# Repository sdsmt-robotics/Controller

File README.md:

# ARCHIVED. USE GITLAB.

# Controller
Repo is used to document all the iterations for the controller

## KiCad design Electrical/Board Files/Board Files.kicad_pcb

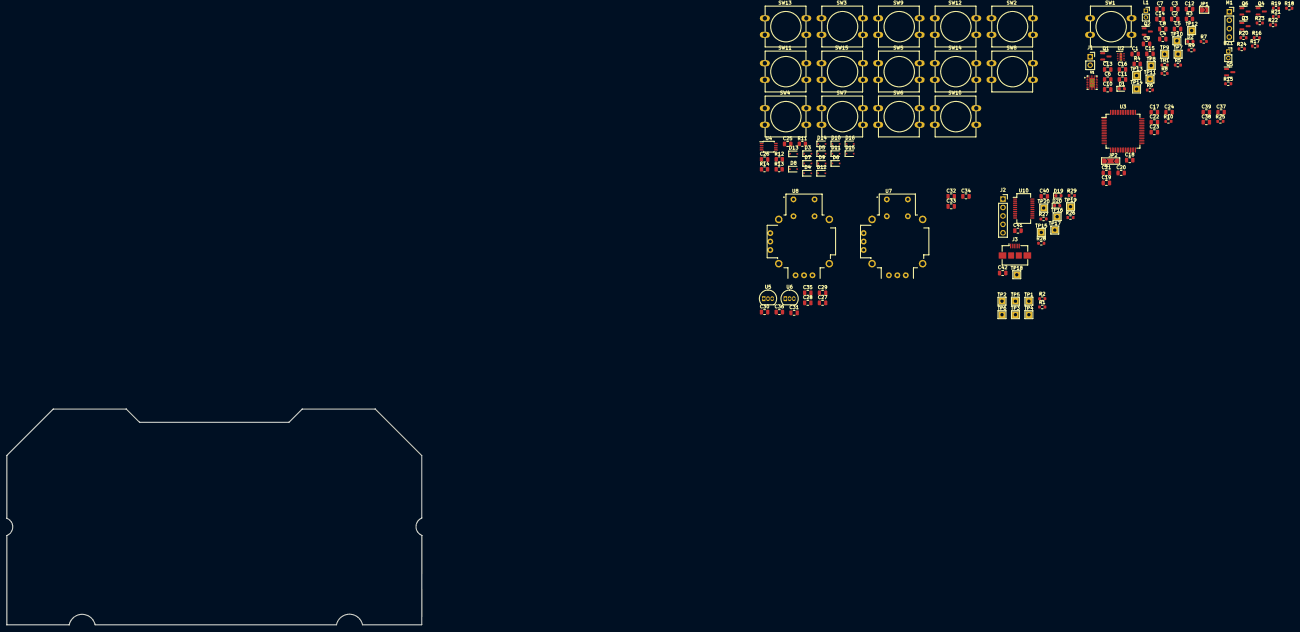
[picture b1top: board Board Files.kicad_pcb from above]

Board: 2 copper layers, 125.1 x 65.0 mm, 148 parts (0 on the bottom side), 94 nets, no tracks yet.

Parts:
BZ1: Buzzer; PinSocket_1x02_P2.00mm_Vertical
C1, C5, C6, C13, C19, C20, C25, C27, C29, C30, C31, C32, C35, C37, C38, C40: 1u; C_0805_2012Metric
C2, C7, C8, C9, C11, C21, C22, C23, C24, C26, C33, C34, C41, C42: 0.1u; C_0805_2012Metric
C3, C4, C10, C12, C17, C18, C39: 10u; C_0805_2012Metric
C14, C15, C16: 22u; C_0805_2012Metric
C28, C36: 0.01u; C_0805_2012Metric
D1: CHARGE_LED; LED_0603_1608Metric
D2: PWR_LED; LED_0603_1608Metric
D3, D4, D5, D6, D7, D8, D9, D10, D11, D12, D13, D14, D15, D16: BAT54J; D_SOD-323F
D19: RX_LED; LED_0603_1608Metric
D20: TX_LED; LED_0603_1608Metric
J1: BATT; PinSocket_1x02_P2.54mm_Vertical
J2: DEBUG; PinSocket_1x05_P2.54mm_Vertical
J3: USB_B_Micro; USB_Micro-B_Amphenol_10104110_Horizontal
JP1: SolderJumper_3_Open; SolderJumper-2_P1.3mm_Open_TrianglePad1.0x1.5mm
JP2: SolderJumper_2_Open; SolderJumper-3_P2.0mm_Open_TrianglePad1.0x1.5mm
L1: 1.5uH; PinSocket_1x02_P2.00mm_Vertical
M1: Motor_DC; PinSocket_1x04_P2.54mm_Vertical
Q1, Q2: PJA3411; SOT-23
Q3, Q4, Q5, Q6: BSS138; SOT-23
R1, R2: 4k; R_0603_1608Metric
R3, R4: 10; R_0805_2012Metric
R5: 1k; R_0603_1608Metric
R6, R7: 220; R_0603_1608Metric
R8: 768k; R_0603_1608Metric
R9: 137k; R_0603_1608Metric
R10, R18, R19, R23, R24, R25: 10k; R_0603_1608Metric
R11, R12, R13, R14: 10k; R_0805_2012Metric
R15, R20: 30; R_0603_1608Metric
R16, R17, R21, R22: 100; R_0603_1608Metric
R26, R27: 27R; R_0603_1608Metric
R28, R29: 270R; R_0603_1608Metric
SW1: SW_DIP_x01; SW_PUSH-12mm
SW2, SW3, SW4, SW5, SW6, SW7, SW8, SW9, SW10, SW11, SW12, SW13, SW14, SW15: SW_PUSH-12mm
TH1: 47K; R_0603_1608Metric
TP1, TP2, TP3, TP4, TP5, TP6, TP7, TP8, TP9, TP10, TP11, TP12, TP13, TP14, TP15, TP16, TP17, TP18, TP19, TP20: TestPoint; TestPoint_THTPad_2.0x2.0mm_Drill1.0mm
U1: TPS63020; IC_TPS63020DSJR
U2: BQ25050DQCR; WSON-10-1EP_2x3mm_P0.5mm_EP0.84x2.4mm_ThermalVias
U3: STM32L431RCTx; LQFP-64_10x10mm_P0.5mm
U4: 74LVC3G17; TSSOP-8_3x3mm_P0.65mm
U5, U6: DRV5055A2xLPGxQ1; TO-92_Inline
U7, U8: COM-09032; XDCR_COM-09032
U10: FT231XS; SSOP-20_3.9x8.7mm_P0.635mm

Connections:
+3V3: BZ1.1 (-), C1.1, C2.1, C10.1, C12.1, C13.1, C14.1, C15.1, C16.1, C17.1, C18.1, C19.1, C20.1, C21.1, C22.1, C23.1, C24.1, C25.1, C26.1, C27.1, C28.1, C31.1, C32.1, C33.1, C34.1, C35.1, C36.1, C37.1, C38.1, C39.1, D2.2 (A), J2.1, M1.1 (+), Q1.3 (D), Q2.3 (D), R1.1, R2.1, R8.1, R10.1, R25.2, SW1.2, TP9.1, TP13.1, U1.4 (VOUT), U1.5 (VOUT), U2.6 (BAT), U3.1 (VBAT), U3.13 (VDDA), U3.19 (VDD), U3.32 (VDD), U3.48 (VDD), U3.64 (VDD), U4.8 (VCC), U5.1 (VCC), U6.1 (VCC), U7.B1B (S1), U7.B2B (BB), U7.H1, U7.V1, U8.B1B (S1), U8.B2B (BB), U8.H1, U8.V1
/Debug/CTS_B: TP16.1, U10.9 (~CTS)
/Debug/DCD_B: TP19.1, U10.8 (~DCD)
/Debug/DSR_B: TP18.1, U10.7 (~DSR)
/Debug/DTR_B: TP17.1, U10.1 (~DTR)
/Debug/FUART.RX: U3.42 (PA9), U10.20 (TXD)
/Debug/FUART.TX: U3.43 (PA10), U10.4 (RXD)
/Debug/RI_B: TP20.1, U10.5 (~RI)
/Debug/RTS_B: TP15.1, U10.2 (~RTS)
/Debug/RX_LED_B: D19.1 (K), U10.17 (CBUS1)
/Debug/SWD.CLK: J2.3, U3.49 (PA14)
/Debug/SWD.DATA: J2.2, U3.46 (PA13)
/Debug/SWD.NRST: J2.4, JP2.2 (B), R10.2, U3.7 (NRST)
/Debug/TX_LED_B: D20.1 (K), U10.10 (CBUS2)
/Debug/USB_N: R26.2, U10.12 (USBDM)
/Debug/USB_P: R27.2, U10.11 (USBDP)
/Joysticks/HALL1: U3.14 (PA0), U5.3 (OUT)
/Joysticks/HALL2: U3.15 (PA1), U6.3 (OUT)
/Joysticks/JOY_B1: C29.1, U3.30 (PB11), U7.B1A (S2), U7.B2A (BA)
/Joysticks/JOY_B2: C30.1, U3.29 (PB10), U8.B1A (S2), U8.B2A (BA)
/Joysticks/JOY_H1: U3.10 (PC2), U7.H2
/Joysticks/JOY_H2: U3.11 (PC3), U8.H2
/Joysticks/JOY_V1: U3.8 (PC0), U7.V2
/Joysticks/JOY_V2: U3.9 (PC1), U8.V2
/LED/COIL.BUZZ: R16.2, R19.1, U3.38 (PC7)
/LED/COIL.VIBE: R22.2, R24.1, U3.37 (PC6)
/MCU/CHG_CTRL: U2.7 (CTRL), U3.41 (PA8)
/MCU/COL1: U3.27 (PB1), U4.7
/MCU/COL2: U3.28 (PB2), U4.2
/MCU/I2C1.SCL: R1.2, TP2.1, U3.61 (PB8)
/MCU/I2C1.SDA: R2.2, TP1.1, U3.62 (PB9)
/MCU/PWM_CH1: R17.2, R18.1, U3.50 (PA15)
/MCU/PWM_CH2: R21.2, R23.1, U3.55 (PB3)
/MCU/ROW1: SW2.1, SW9.1, U3.20 (PA4)
/MCU/ROW2: SW3.1, SW10.1, U3.21 (PA5)
/MCU/ROW3: SW4.1, SW11.1, U3.22 (PA6)
/MCU/ROW4: SW5.1, SW12.1, U3.23 (PA7)
/MCU/ROW5: SW6.1, SW13.1, U3.24 (PC4)
/MCU/ROW6: SW7.1, SW14.1, U3.25 (PC5)
/MCU/ROW7: SW8.1, SW15.1, U3.26 (PB0)
/MCU/SPI2.CS: TP6.1, U3.33 (PB12)
/MCU/SPI2.MISO: TP5.1, U3.35 (PB14)
/MCU/SPI2.MOSI: TP3.1, U3.34 (PB13)
/MCU/SPI2.SCK: TP4.1, U3.36 (PB15)
/Power/BGATE: R3.1, R4.1, TP12.1, U2.9 (BGATE)
/Power/CHG_OUT: C11.1, JP1.1 (A), Q1.2 (S), Q2.2 (S), TP14.1
/Power/TPS_FB: R8.2, R9.1, TP11.1, U1.3 (FB)
GND: C1.2, C2.2, C3.2, C4.2, C5.2, C6.2, C7.2, C8.2, C9.2, C10.2, C11.2, C12.2, C13.2, C14.2, C15.2, C16.2, C17.2, C18.2, C19.2, C20.2, C21.2, C22.2, C23.2, C24.2, C25.2, C26.2, C27.2, C28.2, C29.2, C30.2, C31.2, C32.2, C33.2, C34.2, C35.2, C36.2, C37.2, C38.2, C39.2, C40.2, C41.2, C42.2, J1.1, J2.5, J3.4 (ID), J3.5 (GND), J3.6 (Shield), JP2.1 (A), Q3.2 (S), Q4.2 (S), Q5.2 (S), Q6.2 (S), R5.2, R9.2, R11.2, R12.2, R13.2, R14.2, R18.2, R19.2, R23.2, R24.2, TH1.1, U1.2 (GND), U1.13 (PGND), U2.3 (VSS), U3.12 (VSSA), U3.18 (VSS), U3.31 (VSS), U3.47 (VSS), U3.63 (VSS), U4.4 (GND), U5.2 (GND), U6.2 (GND), U7.H3, U7.S1 (MOUNT), U7.S2 (MOUNT), U7.S3 (MOUNT), U7.S4 (MOUNT), U7.V3, U8.H3, U8.S1 (MOUNT), U8.S2 (MOUNT), U8.S3 (MOUNT), U8.S4 (MOUNT), U8.V3, U10.6 (GND), U10.16 (GND)
unnamed: BZ1.2 (+), Q3.3 (D)
unnamed: C3.1, C4.1, C5.1, JP1.2 (C), TP7.1, U1.10 (VIN), U1.11 (VIN)
unnamed: C7.1, U1.1 (VINA), U1.12 (EN)
unnamed: C9.1, TP10.1, U2.4 (LDO)
unnamed: C40.1, U10.3 (VCCIO), U10.13 (3V3OUT), U10.14 (~RESET)
unnamed: D1.1 (K), U2.8 (CHG_B)
unnamed: D1.2 (A), R6.2
unnamed: D2.1 (K), R7.2
unnamed: D19.2 (A), R28.2
unnamed: D20.2 (A), R29.2
unnamed: J1.2, SW1.1
unnamed: J3.2 (D-), R26.1
unnamed: J3.3 (D+), R27.1
unnamed: L1.1, U1.8 (L1), U1.9 (L1)
unnamed: L1.2, U1.6 (L2), U1.7 (L2)
unnamed: M1.2 (-), Q5.3 (D)
unnamed: Q1.1 (G), R3.2
unnamed: Q2.1 (G), R4.2
unnamed: Q3.1 (G), R16.1
unnamed: Q4.1 (G), R17.1
unnamed: Q4.3 (D), R15.2
unnamed: Q5.1 (G), R22.1
unnamed: Q6.1 (G), R21.1
unnamed: Q6.3 (D), R20.2
unnamed: R5.1, TP8.1, U2.2 (IMON)
unnamed: R7.1, U1.14 (PG)
unnamed: D3.1 (K), D4.1 (K), D5.1 (K), D6.1 (K), D7.1 (K), D8.1 (K), D9.1 (K), R11.1, U4.1
unnamed: D10.1 (K), D11.1 (K), D12.1 (K), D13.1 (K), D14.1 (K), D15.1 (K), D16.1 (K), R12.1, U4.6
unnamed: R13.1, U4.3
unnamed: R14.1, U4.5
unnamed: D3.2 (A), SW2.2
unnamed: D4.2 (A), SW3.2
unnamed: D5.2 (A), SW4.2
unnamed: D6.2 (A), SW5.2
unnamed: D7.2 (A), SW6.2
unnamed: D8.2 (A), SW7.2
unnamed: D9.2 (A), SW8.2
unnamed: D10.2 (A), SW9.2
unnamed: D11.2 (A), SW10.2
unnamed: D12.2 (A), SW11.2
unnamed: D13.2 (A), SW12.2
unnamed: D14.2 (A), SW13.2
unnamed: D15.2 (A), SW14.2
unnamed: D16.2 (A), SW15.2
unnamed: TH1.2, U2.5 (TS)
VBUS: C6.1, C8.1, C41.1, C42.1, J3.1 (VBUS), R6.1, R28.1, R29.1, U2.1 (Vin), U10.15 (VCC)

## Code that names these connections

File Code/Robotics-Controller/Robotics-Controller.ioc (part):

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Mcu.Name=STM32L431R(B-C)Tx
Mcu.Package=LQFP64
Mcu.UserName=STM32L431RCTx
PA0.GPIOParameters=GPIO_Label
PA0.GPIO_Label=HALL_1
PA0.Signal=ADCx_IN5
PA1.GPIOParameters=GPIO_Label
PA1.GPIO_Label=HALL_2
PA1.Signal=ADCx_IN6
PA10.GPIOParameters=GPIO_Label
PA10.GPIO_Label=MCU_RX
PA10.Mode=Asynchronous
PA10.Signal=USART1_RX
PA11.GPIOParameters=GPIO_Label
PA11.GPIO_Label=LED1
PA11.Signal=GPIO_Output
PA12.GPIOParameters=GPIO_Label
PA12.GPIO_Label=LED2
PA12.Signal=GPIO_Output
PA13\ (JTMS-SWDIO).Mode=Serial_Wire
PA13\ (JTMS-SWDIO).Signal=SYS_JTMS-SWDIO
PA14\ (JTCK-SWCLK).Mode=Serial_Wire
PA14\ (JTCK-SWCLK).Signal=SYS_JTCK-SWCLK
PA15\ (JTDI).GPIOParameters=GPIO_Label
PA15\ (JTDI).GPIO_Label=PWM_CH1
PA15\ (JTDI).Signal=S_TIM2_CH1
PA2.GPIOParameters=GPIO_Label
PA2.GPIO_Label=VBAT
PA2.Signal=ADCx_IN7
PA4.GPIOParameters=GPIO_Label
PA4.GPIO_Label=R1
PA4.Signal=GPIO_Output
PA5.GPIOParameters=GPIO_Label
PA5.GPIO_Label=R2
PA5.Signal=GPIO_Output
PA6.GPIOParameters=GPIO_Label
PA6.GPIO_Label=R3
PA6.Signal=GPIO_Output
PA7.GPIOParameters=GPIO_Label
PA7.GPIO_Label=R4
PA7.Signal=GPIO_Output
PA8.GPIOParameters=GPIO_Label
PA8.GPIO_Label=CHG_CTRL
PA8.Signal=GPIO_Output
PA9.GPIOParameters=GPIO_Label
PA9.GPIO_Label=MCU_TX
PA9.Mode=Asynchronous
PA9.Signal=USART1_TX
PB0.GPIOParameters=GPIO_Label
PB0.GPIO_Label=R7
PB0.Signal=GPIO_Output
PB1.GPIOParameters=GPIO_Label
PB1.GPIO_Label=C1
PB1.Signal=GPIO_Input
PB10.GPIOParameters=GPIO_Label
PB10.GPIO_Label=JOY_B2
PB10.Signal=GPIO_Input
PB11.GPIOParameters=GPIO_Label
PB11.GPIO_Label=JOY_B1
PB11.Signal=GPIO_Input
PB13.Mode=Full_Duplex_Master
PB13.Signal=SPI2_SCK
PB14.Mode=Full_Duplex_Master
PB14.Signal=SPI2_MISO
PB15.Mode=Full_Duplex_Master
PB15.Signal=SPI2_MOSI
PB2.GPIOParameters=GPIO_Label
PB2.GPIO_Label=C2
PB2.Signal=GPIO_Input
PB3\ (JTDO-TRACESWO).GPIOParameters=GPIO_Label
PB3\ (JTDO-TRACESWO).GPIO_Label=PWM_CH2
PB3\ (JTDO-TRACESWO).Signal=S_TIM2_CH2
PB4\ (NJTRST).GPIOParameters=GPIO_Label
PB4\ (NJTRST).GPIO_Label=LED3
PB4\ (NJTRST).Signal=GPIO_Output
PB5.GPIOParameters=GPIO_Label
PB5.GPIO_Label=LED4
PB5.Signal=GPIO_Output
PB6.GPIOParameters=GPIO_Label
PB6.GPIO_Label=LED5
PB6.Signal=GPIO_Output
PB7.GPIOParameters=GPIO_Label
PB7.GPIO_Label=LED6
PB7.Signal=GPIO_Output
PB8.Mode=I2C
PB8.Signal=I2C1_SCL
PB9.Mode=I2C
PB9.Signal=I2C1_SDA
PC0.GPIOParameters=GPIO_Label
PC0.GPIO_Label=JOY_V1
PC0.Signal=ADCx_IN1
PC1.GPIOParameters=GPIO_Label
PC1.GPIO_Label=JOY_V2
PC1.Signal=ADCx_IN2
PC10.GPIOParameters=GPIO_Label
PC10.GPIO_Label=UART_TX
PC10.Mode=Asynchronous
PC10.Signal=USART3_TX
PC11.GPIOParameters=GPIO_Label
PC11.GPIO_Label=UART_RX
PC11.Mode=Asynchronous
PC11.Signal=USART3_RX
PC2.GPIOParameters=GPIO_Label
PC2.GPIO_Label=JOY_H1
PC2.Signal=ADCx_IN3
PC3.GPIOParameters=GPIO_Label
PC3.GPIO_Label=JOY_H2
PC3.Signal=ADCx_IN4
PC4.GPIOParameters=GPIO_Label
PC4.GPIO_Label=R5
PC4.Signal=GPIO_Output
PC5.GPIOParameters=GPIO_Label
PC5.GPIO_Label=R6
PC5.Signal=GPIO_Output
PC6.GPIOParameters=GPIO_Label
PC6.GPIO_Label=VIBE
PC6.Signal=GPIO_Output
PC7.GPIOParameters=GPIO_Label
PC7.GPIO_Label=BUZZER
PC7.Signal=GPIO_Output
RCC.HSE_VALUE=8000000
RCC.SYSCLKFreq_VALUE=64000000
RCC.SYSCLKSource=RCC_SYSCLKSOURCE_PLLCLK
board=custom

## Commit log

2019-09-14 Added buttons and a switch
2019-09-15 Redid debounce filter and added unity gain buffer. Added Xbee and logic level shifter for RX and TX
2019-09-15 Added 16MHz oscillator for Atmega328p
2019-09-15 Fixed connection error in Low Pass filter
2019-10-05 Update Controller.lbr
    Made a couple of changes to the board outline. Add zeners to the each button
2019-10-11 Added more holes, did some routing added 3D models
2019-10-11 MORE ROUTING!!
2019-10-12 Routing
    Routed most of the board. Need to add power components and Zeners
2019-10-19 Changes
    Added more 3D models. Changed to a ATMega2560
2019-10-20 Added Charlieplexed button matrix
    Will now have to turn on PORTB bits 1:3
2019-10-20 Added Hall effect sensors
2019-10-21 Redoing the board
2019-10-24 Added Board
2019-10-24 added 5V regulator
    Still need to add BMS circuitry and switch
2019-10-28 rerouted so we only have 2 layers, added PWM pin
    Need to add battery switch,indicator Vbat pins
2019-11-01 Added switch and LED
2019-11-02 finished?
2019-11-02 Added a License
2019-11-02 Added coherent BOM
2019-11-03 Added diodes and made traces 10 mills
2019-11-03 Minor Changes and added Gerber
2019-11-04 Updated trace width for power
    All Power traces (VCC, +3V3 and 5V) are rated for 1.5A. All other traces are rated for 0.8A
2019-11-04 Added Gerbers
2019-11-04 Added Sam's holes
2019-11-04 Read Desc.
    * Moved Bumpers 3mm lower
    * changed TO diodes to SMD
    * Chnaged BOM to shorter actuator buttons
2019-11-21 Fixed overlap and deleted some stubs
2019-12-09 Finished code? Needs to be tested
2020-01-13 Fixed pin toggeling
    Had to NOT some bits to set the pin LOW
2020-01-18 Tested
2020-02-02 Update sketch_dec04a.ino
    Mostly working controller code. Still have to fix recieving more than one button press when only pressed once. Must also make sure hall effect sensors work.
2020-02-29 Debounced buttons
    Hopefully, it's done and I don't need to adjust any delays
2020-03-01 FIxed
    Have Sam check
2020-03-13 Fix formatting in README
2020-03-13 Add communications code and documentation
2020-03-14 Fix missing joystick button in receive demo code
2020-03-14 Add code for rev3 of the controller
2020-03-15 Improve data transmission and add some functions to clean up analog values
    * Increased xbee baudrate to 115200. Nothing has caught on fire yet...
    * Split full sends into two halves so we are less likely to overflow the serial buffer.
    * Added a joystick deadzone function to the receive code
    * Changed over to floats for analog values. Performance doesn't take that much of a hit, and it is much more usable.
    * Added some scaling to analog values for rev3.
    * Added some documentation for the rev3 code.
2020-03-16 Add (mostly) working rev2 code
2020-03-17 Update documentation to add rev2 notes
2020-03-17 Add button debouncing to rev2 code
2020-08-26 Add changes to example receive code
2020-12-31 Remove debugging stuff
2022-06-14 Addimg readme
2022-06-14 Updating README
2022-06-14 Test commit
2022-08-19 Adding new block diagram
2022-08-28 Updating Files
2022-08-28 Adding CubeMX config file and generated code
2022-08-31 Updating for 3v3 operation
2022-08-31 Adding power dissipation notes. Removing WS2821B since they won't work with a 3v3 supply
2022-08-31 updating label directions
2022-09-01 Added buzz and vibe, moved SPI, added 2 LEDs
2022-09-01 Updating sheet template
2022-09-01 added switch
2022-09-02 Added Xbee libs and bus aliases
2022-09-02 Updating title block fields and adding pdf schematic
2022-09-02 Adding Block svg
2022-09-07 Adding pull ups on I2C lines
2022-09-25 Fixing USB pins and added SPI_CS
2022-09-25 Adding some device footprints and MPN
2022-10-15 No clue what changed
2022-10-21 Removed unnecessary FETs
2022-11-25 Adding footprints
2022-12-03 fix relative path for template
2022-12-03 archive
